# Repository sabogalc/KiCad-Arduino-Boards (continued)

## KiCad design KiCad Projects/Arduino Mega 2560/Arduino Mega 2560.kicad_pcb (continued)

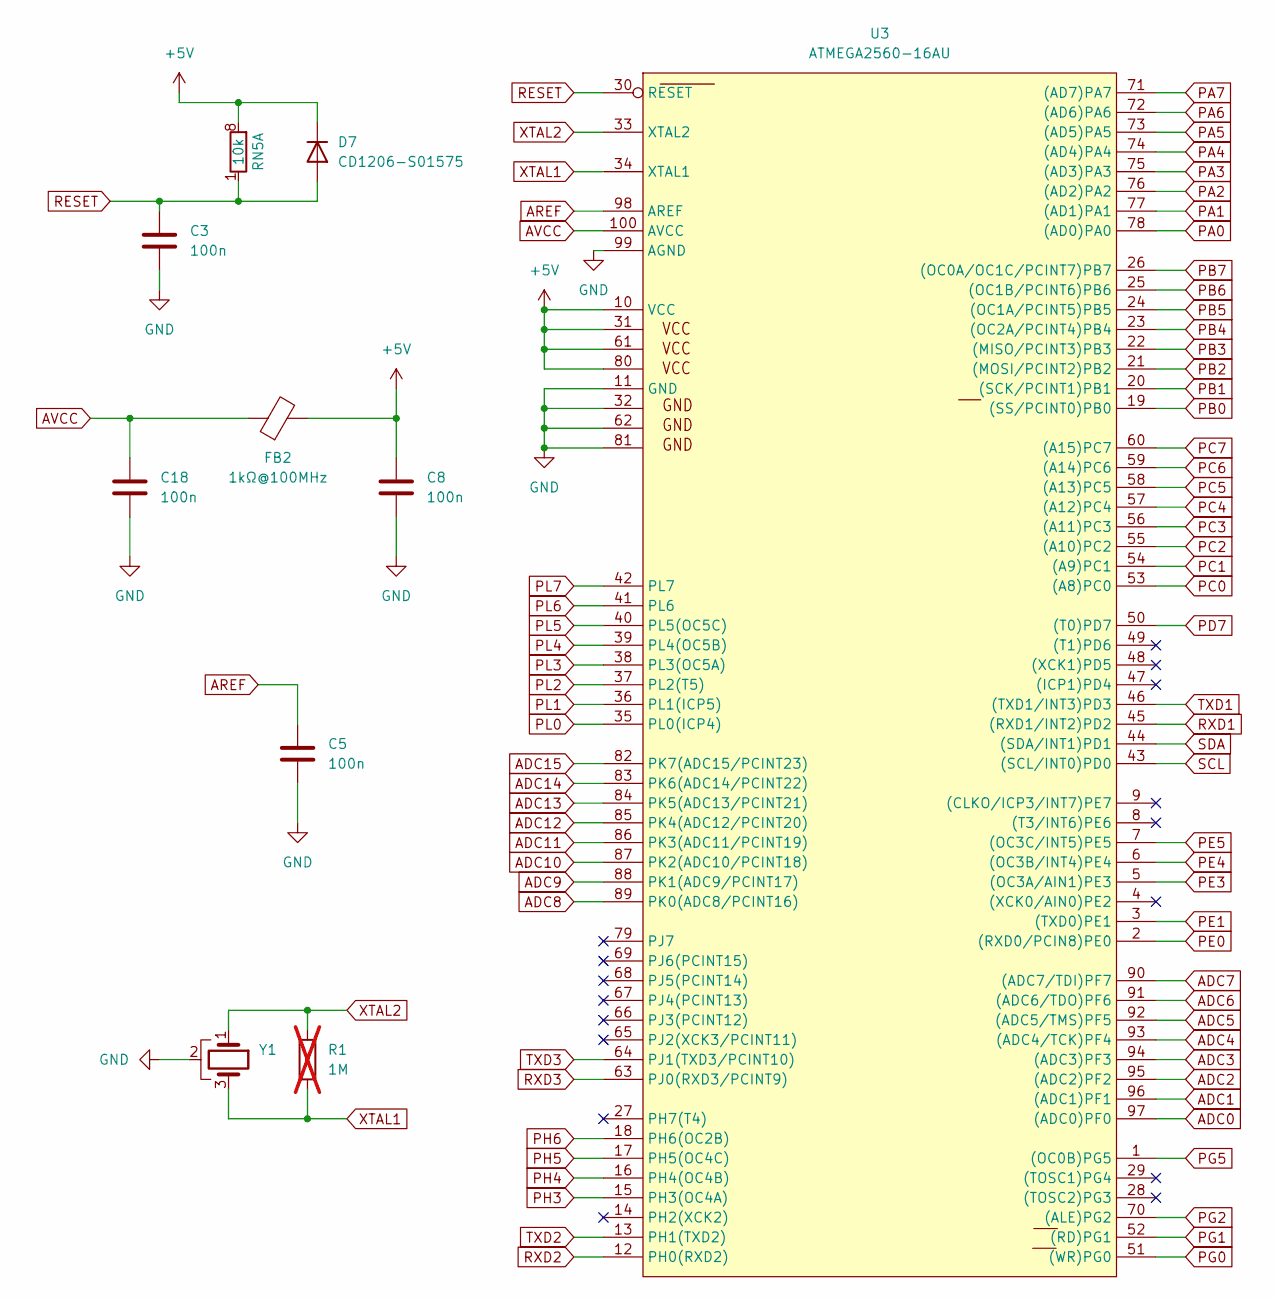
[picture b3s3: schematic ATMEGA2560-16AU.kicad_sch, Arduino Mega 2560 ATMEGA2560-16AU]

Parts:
C3, C5, C8, C18: 100n; C_0603_1608Metric
D7: CD1206-S01575; D_1206_3216Metric
FB2: 1kΩ@100MHz; L_0805_2012Metric
R1: 1M; R_0603_1608Metric; not fitted
RN5: 10k; R_Array_Convex_4x0612
U3: ATMEGA2560-16AU; TQFP-100_14x14mm_P0.5mm
Y1: CSTNE16M0V530000R0; Resonator_SMD_Murata_CSTxExxV-3Pin_3.0x1.1mm

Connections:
+5V: C8.1, D7.1 (K), FB2.2, RN5.8 (R1.2), U3.10 (VCC), U3.31 (VCC1), U3.61 (VCC2), U3.80 (VCC3); also elsewhere on the board
ADC0: U3.97 ((ADC0)PF0); also elsewhere on the board
ADC1: U3.96 ((ADC1)PF1); also elsewhere on the board
ADC2: U3.95 ((ADC2)PF2); also elsewhere on the board
ADC3: U3.94 ((ADC3)PF3); also elsewhere on the board
ADC4: U3.93 ((ADC4/TCK)PF4); also elsewhere on the board
ADC5: U3.92 ((ADC5/TMS)PF5); also elsewhere on the board
ADC6: U3.91 ((ADC6/TDO)PF6); also elsewhere on the board
ADC7: U3.90 ((ADC7/TDI)PF7); also elsewhere on the board
ADC8: U3.89 (PK0(ADC8/PCINT16)); also elsewhere on the board
ADC9: U3.88 (PK1(ADC9/PCINT17)); also elsewhere on the board
ADC10: U3.87 (PK2(ADC10/PCINT18)); also elsewhere on the board
ADC11: U3.86 (PK3(ADC11/PCINT19)); also elsewhere on the board
ADC12: U3.85 (PK4(ADC12/PCINT20)); also elsewhere on the board
ADC13: U3.84 (PK5(ADC13/PCINT21)); also elsewhere on the board
ADC14: U3.83 (PK6(ADC14/PCINT22)); also elsewhere on the board
ADC15: U3.82 (PK7(ADC15/PCINT23)); also elsewhere on the board
AREF: C5.1, U3.98 (AREF); also elsewhere on the board
AVCC: C18.1, FB2.1, U3.100 (AVCC)
GND: C3.2, C5.2, C8.2, C18.2, U3.11 (GND), U3.32 (GND1), U3.62 (GND2), U3.81 (GND3), U3.99 (AGND), Y1.2; also elsewhere on the board
PA0: U3.78 ((AD0)PA0); also elsewhere on the board
PA1: U3.77 ((AD1)PA1); also elsewhere on the board
PA2: U3.76 ((AD2)PA2); also elsewhere on the board
PA3: U3.75 ((AD3)PA3); also elsewhere on the board
PA4: U3.74 ((AD4)PA4); also elsewhere on the board
PA5: U3.73 ((AD5)PA5); also elsewhere on the board
PA6: U3.72 ((AD6)PA6); also elsewhere on the board
PA7: U3.71 ((AD7)PA7); also elsewhere on the board
PB0: U3.19 ((SS/PCINT0)PB0); also elsewhere on the board
PB1: U3.20 ((SCK/PCINT1)PB1); also elsewhere on the board
PB2: U3.21 ((MOSI/PCINT2)PB2); also elsewhere on the board
PB3: U3.22 ((MISO/PCINT3)PB3); also elsewhere on the board
PB4: U3.23 ((OC2A/PCINT4)PB4); also elsewhere on the board
PB5: U3.24 ((OC1A/PCINT5)PB5); also elsewhere on the board
PB6: U3.25 ((OC1B/PCINT6)PB6); also elsewhere on the board
PB7: U3.26 ((OC0A/OC1C/PCINT7)PB7); also elsewhere on the board
PC0: U3.53 ((A8)PC0); also elsewhere on the board
PC1: U3.54 ((A9)PC1); also elsewhere on the board
PC2: U3.55 ((A10)PC2); also elsewhere on the board
PC3: U3.56 ((A11)PC3); also elsewhere on the board
PC4: U3.57 ((A12)PC4); also elsewhere on the board
PC5: U3.58 ((A13)PC5); also elsewhere on the board
PC6: U3.59 ((A14)PC6); also elsewhere on the board
PC7: U3.60 ((A15)PC7); also elsewhere on the board
PD7: U3.50 ((T0)PD7); also elsewhere on the board
PE0: U3.2 ((RXD0/PCIN8)PE0); also elsewhere on the board
PE1: U3.3 ((TXD0)PE1); also elsewhere on the board
PE3: U3.5 ((OC3A/AIN1)PE3); also elsewhere on the board
PE4: U3.6 ((OC3B/INT4)PE4); also elsewhere on the board
PE5: U3.7 ((OC3C/INT5)PE5); also elsewhere on the board
PG0: U3.51 ((WR)PG0); also elsewhere on the board
PG1: U3.52 ((RD)PG1); also elsewhere on the board
PG2: U3.70 ((ALE)PG2); also elsewhere on the board
PG5: U3.1 ((OC0B)PG5); also elsewhere on the board
PH3: U3.15 (PH3(OC4A)); also elsewhere on the board
PH4: U3.16 (PH4(OC4B)); also elsewhere on the board
PH5: U3.17 (PH5(OC4C)); also elsewhere on the board
PH6: U3.18 (PH6(OC2B)); also elsewhere on the board
PL0: U3.35 (PL0(ICP4)); also elsewhere on the board
PL1: U3.36 (PL1(ICP5)); also elsewhere on the board
PL2: U3.37 (PL2(T5)); also elsewhere on the board
PL3: U3.38 (PL3(OC5A)); also elsewhere on the board
PL4: U3.39 (PL4(OC5B)); also elsewhere on the board
PL5: U3.40 (PL5(OC5C)); also elsewhere on the board
PL6: U3.41 (PL6); also elsewhere on the board
PL7: U3.42 (PL7); also elsewhere on the board
RESET: C3.1, D7.2 (A), RN5.1 (R1.1), U3.30 (RESET); also elsewhere on the board
RXD1: U3.45 ((RXD1/INT2)PD2); also elsewhere on the board
RXD2: U3.12 (PH0(RXD2)); also elsewhere on the board
RXD3: U3.63 (PJ0(RXD3/PCINT9)); also elsewhere on the board
SCL: U3.43 ((SCL/INT0)PD0); also elsewhere on the board
SDA: U3.44 ((SDA/INT1)PD1); also elsewhere on the board
TXD1: U3.46 ((TXD1/INT3)PD3); also elsewhere on the board
TXD2: U3.13 (PH1(TXD2)); also elsewhere on the board
TXD3: U3.64 (PJ1(TXD3/PCINT10)); also elsewhere on the board
XTAL1: R1.1, U3.34 (XTAL1), Y1.3
XTAL2: R1.2, U3.33 (XTAL2), Y1.1

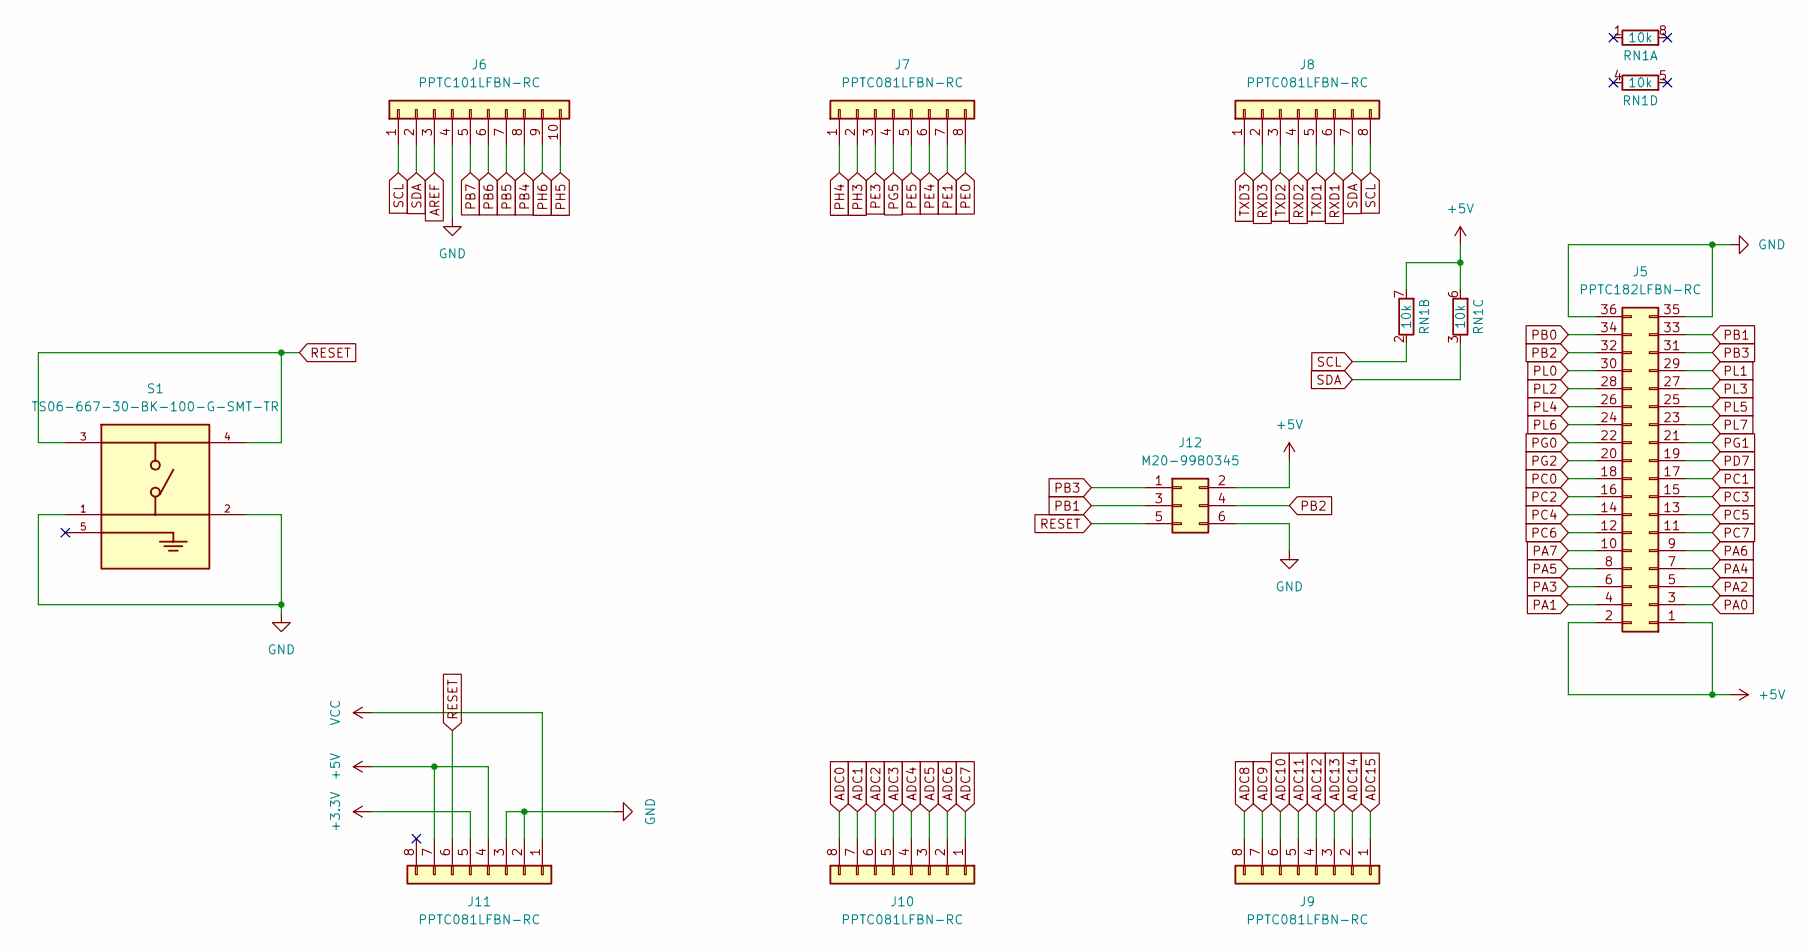
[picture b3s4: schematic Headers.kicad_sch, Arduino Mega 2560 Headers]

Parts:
J5: PPTC182LFBN-RC
J6: PPTC101LFBN-RC; PinSocket_1x10_P2.54mm_Vertical
J7, J8, J9, J10, J11: PPTC081LFBN-RC; PinSocket_1x08_P2.54mm_Vertical
J12: M20-9980345; PinHeader_2x03_P2.54mm_Vertical
RN1: 10k; R_Array_Convex_4x0612
S1: TS06-667-30-BK-100-G-SMT-TR; SW_TS06-667-30-BK-100-G-SMT-TR; PARTREV 1.0

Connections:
+3.3V: J11.5; also elsewhere on the board
+5V: J5.1, J5.2, J11.4, J11.7, J12.2, RN1.6 (R3.2), RN1.7 (R2.2); also elsewhere on the board
ADC0: J10.8; also elsewhere on the board
ADC1: J10.7; also elsewhere on the board
ADC2: J10.6; also elsewhere on the board
ADC3: J10.5; also elsewhere on the board
ADC4: J10.4; also elsewhere on the board
ADC5: J10.3; also elsewhere on the board
ADC6: J10.2; also elsewhere on the board
ADC7: J10.1; also elsewhere on the board
ADC8: J9.8; also elsewhere on the board
ADC9: J9.7; also elsewhere on the board
ADC10: J9.6; also elsewhere on the board
ADC11: J9.5; also elsewhere on the board
ADC12: J9.4; also elsewhere on the board
ADC13: J9.3; also elsewhere on the board
ADC14: J9.2; also elsewhere on the board
ADC15: J9.1; also elsewhere on the board
AREF: J6.3; also elsewhere on the board
GND: J5.35, J5.36, J6.4, J11.2, J11.3, J12.6, S1.1, S1.2; also elsewhere on the board
PA0: J5.3; also elsewhere on the board
PA1: J5.4; also elsewhere on the board
PA2: J5.5; also elsewhere on the board
PA3: J5.6; also elsewhere on the board
PA4: J5.7; also elsewhere on the board
PA5: J5.8; also elsewhere on the board
PA6: J5.9; also elsewhere on the board
PA7: J5.10; also elsewhere on the board
PB0: J5.34; also elsewhere on the board
PB1: J5.33, J12.3; also elsewhere on the board
PB2: J5.32, J12.4; also elsewhere on the board
PB3: J5.31, J12.1; also elsewhere on the board
PB4: J6.8; also elsewhere on the board
PB5: J6.7; also elsewhere on the board
PB6: J6.6; also elsewhere on the board
PB7: J6.5; also elsewhere on the board
PC0: J5.18; also elsewhere on the board
PC1: J5.17; also elsewhere on the board
PC2: J5.16; also elsewhere on the board
PC3: J5.15; also elsewhere on the board
PC4: J5.14; also elsewhere on the board
PC5: J5.13; also elsewhere on the board
PC6: J5.12; also elsewhere on the board
PC7: J5.11; also elsewhere on the board
PD7: J5.19; also elsewhere on the board
PE0: J7.8; also elsewhere on the board
PE1: J7.7; also elsewhere on the board
PE3: J7.3; also elsewhere on the board
PE4: J7.6; also elsewhere on the board
PE5: J7.5; also elsewhere on the board
PG0: J5.22; also elsewhere on the board
PG1: J5.21; also elsewhere on the board
PG2: J5.20; also elsewhere on the board
PG5: J7.4; also elsewhere on the board
PH3: J7.2; also elsewhere on the board
PH4: J7.1; also elsewhere on the board
PH5: J6.10; also elsewhere on the board
PH6: J6.9; also elsewhere on the board
PL0: J5.30; also elsewhere on the board
PL1: J5.29; also elsewhere on the board
PL2: J5.28; also elsewhere on the board
PL3: J5.27; also elsewhere on the board
PL4: J5.26; also elsewhere on the board
PL5: J5.25; also elsewhere on the board
PL6: J5.24; also elsewhere on the board
PL7: J5.23; also elsewhere on the board
RESET: J11.6, J12.5, S1.3, S1.4; also elsewhere on the board
RXD1: J8.6; also elsewhere on the board
RXD2: J8.4; also elsewhere on the board
RXD3: J8.2; also elsewhere on the board
SCL: J6.1, J8.8, RN1.2 (R2.1); also elsewhere on the board
SDA: J6.2, J8.7, RN1.3 (R3.1); also elsewhere on the board
TXD1: J8.5; also elsewhere on the board
TXD2: J8.3; also elsewhere on the board
TXD3: J8.1; also elsewhere on the board
VCC: J11.1; also elsewhere on the board

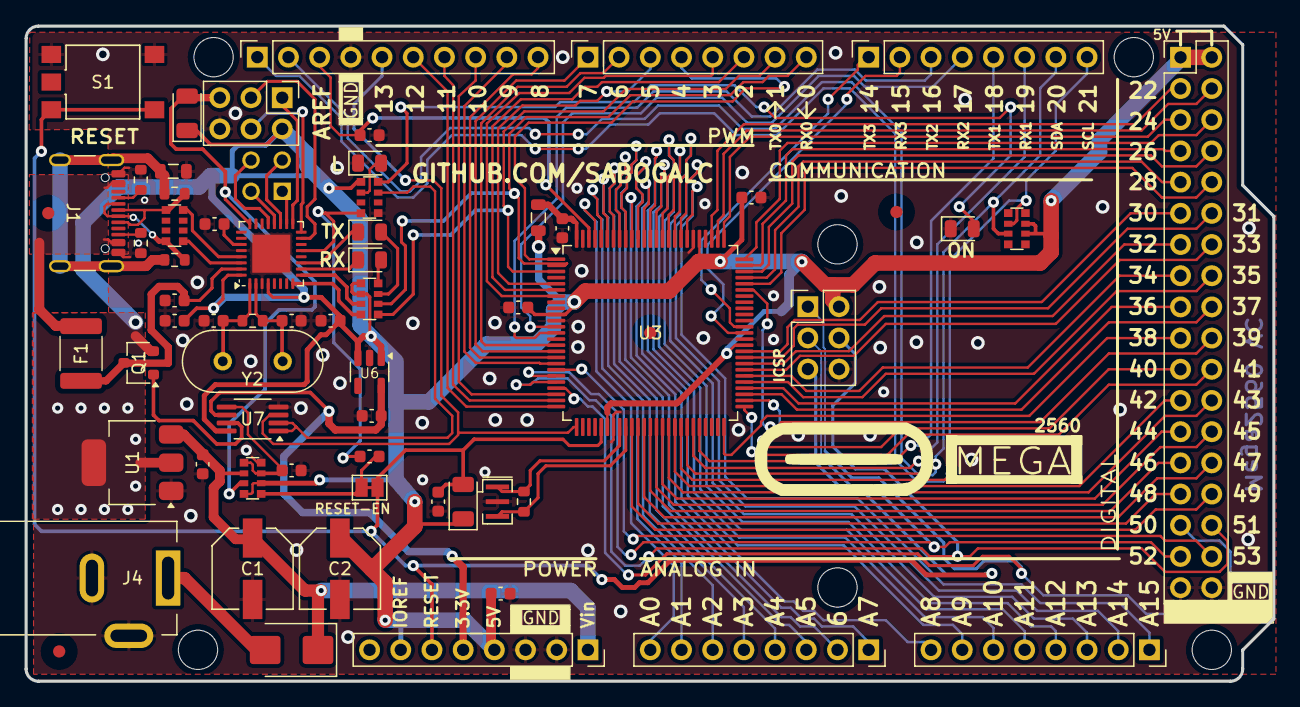
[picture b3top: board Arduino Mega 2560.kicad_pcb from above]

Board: 2 copper layers, 101.6 x 53.3 mm, 66 parts (1 on the bottom side), 112 nets.

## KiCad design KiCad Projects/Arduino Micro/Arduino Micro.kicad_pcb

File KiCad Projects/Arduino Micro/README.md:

# Micro
Much like the Nano, I made this board in one or two sittings.

This board is not much bigger than the Nano, but it brings benefits such as the full-sized reset switch and four more IO pins.

## KiCad 3D View
Below are the screenshots of this board from KiCad's 3D board viewer.

## Real-World Application
Additionally, I have successfully built this board in real life and confirmed that it works.

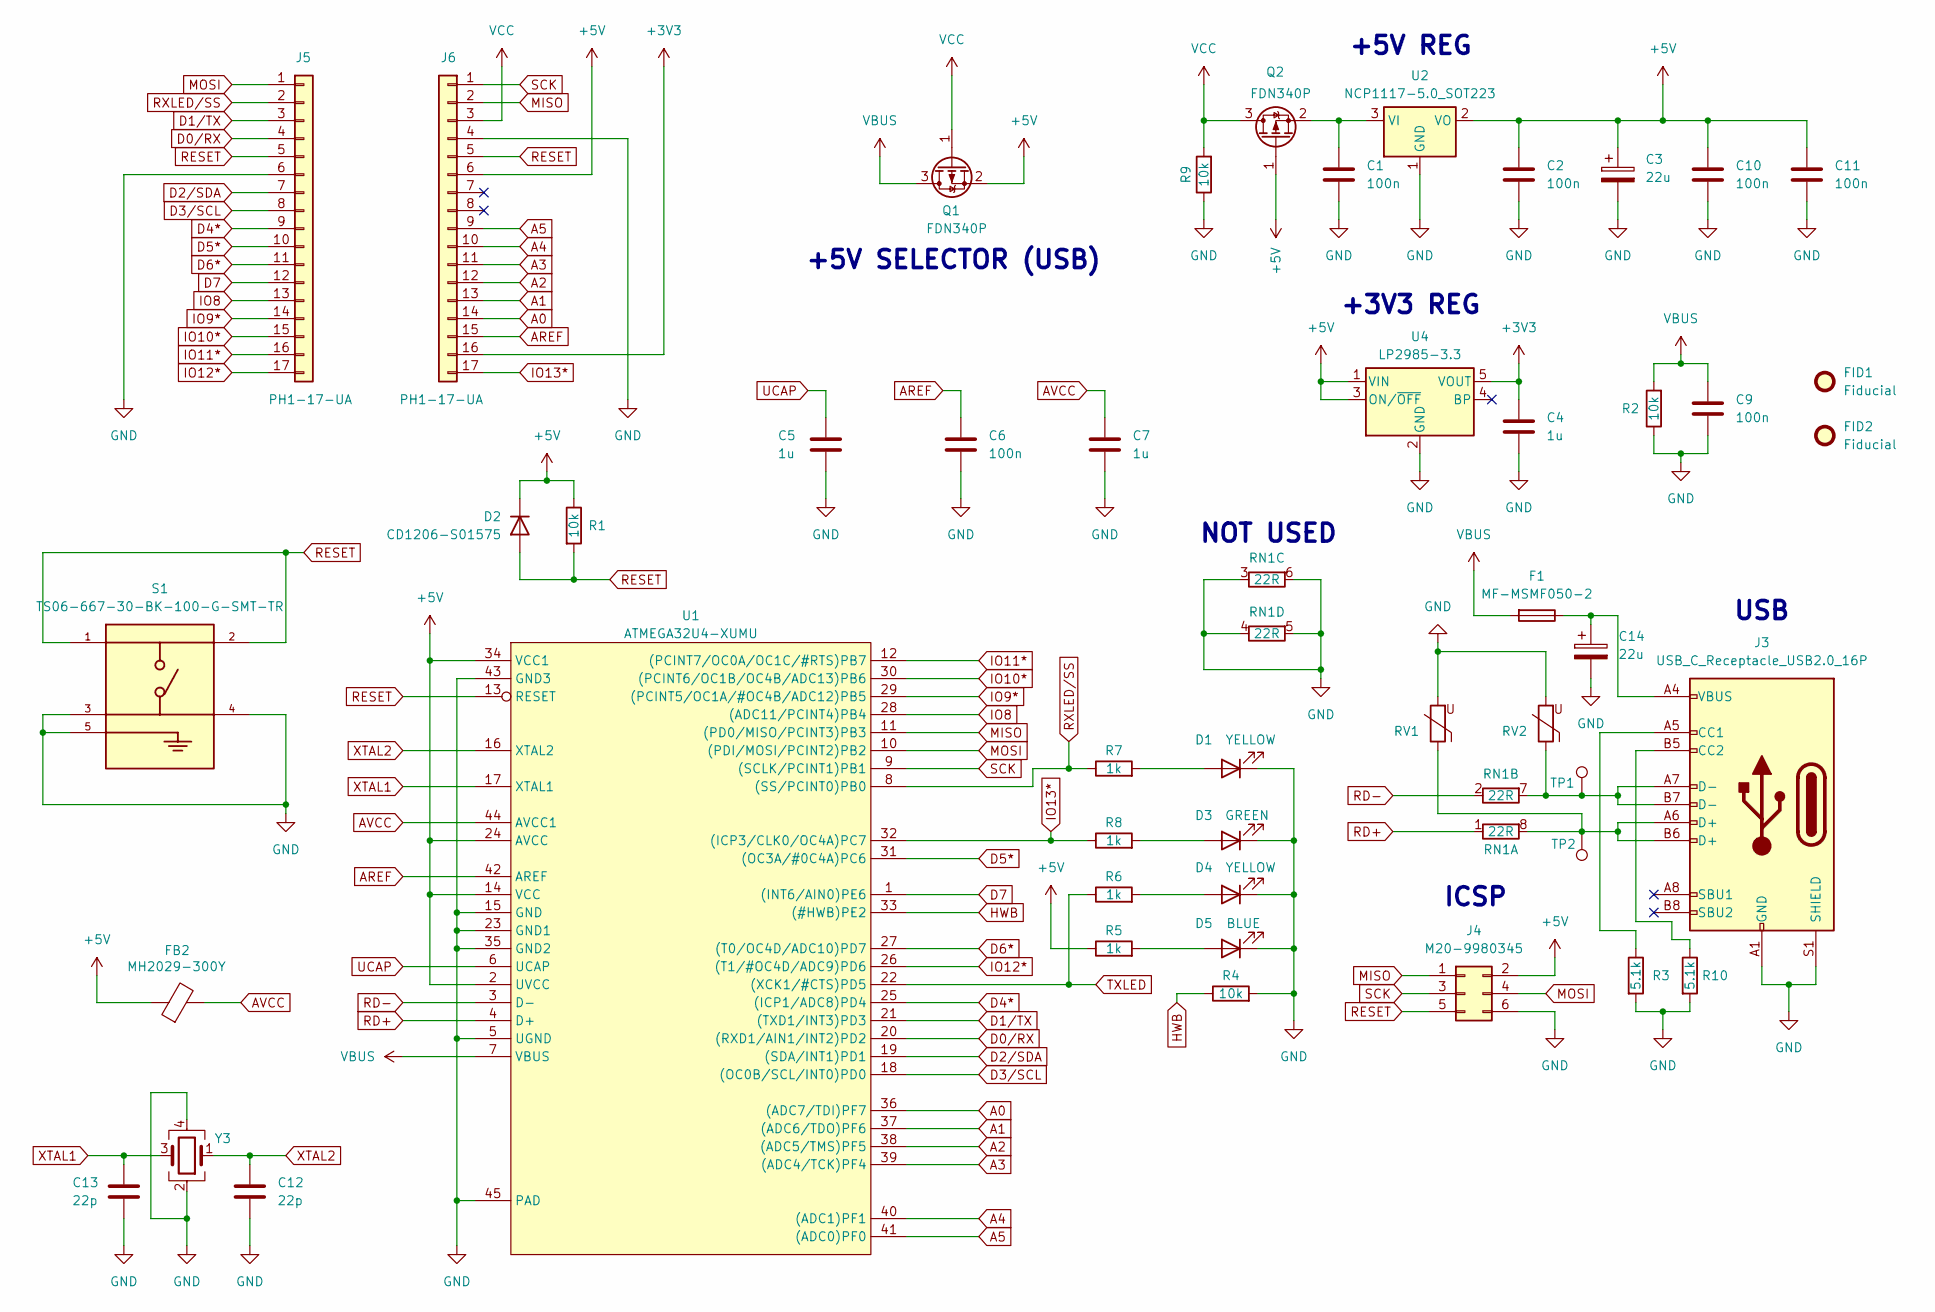
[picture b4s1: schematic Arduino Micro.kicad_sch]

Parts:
C1, C2, C6, C9, C10, C11: 100n; C_0402_1005Metric
C3, C14: 22u; C_1210_3225Metric_Pad1.33x2.70mm_HandSolder
C4, C5, C7: 1u; C_0402_1005Metric
C12, C13: 22p; C_0402_1005Metric
D1, D4: YELLOW; LED_0805_2012Metric
D2: CD1206-S01575; D_1206_3216Metric
D3: GREEN; LED_0805_2012Metric
D5: BLUE; LED_0805_2012Metric
F1: MF-MSMF050-2; Fuse_1812_4532Metric_Pad1.30x3.40mm_HandSolder
FB2: MH2029-300Y; L_0805_2012Metric
FID1, FID2: Fiducial; Fiducial_1mm_Mask2mm
J3: USB_C_Receptacle_USB2.0_16P; USB_C_Receptacle_GCT_USB4110
J4: M20-9980345; PinHeader_2x03_P2.54mm_Vertical
J5, J6: PH1-17-UA; PinHeader_1x17_P2.54mm_Vertical
Q1, Q2: FDN340P; SC-59
R1, R2, R4, R9: 10k; R_0402_1005Metric
R3, R10: 5.1k; R_0402_1005Metric
R5, R6, R7, R8: 1k; R_0402_1005Metric
RN1: 22R; R_Array_Convex_4x0612
RV1, RV2: CG0603MLC-05E; R_0603_1608Metric
S1: TS06-667-30-BK-100-G-SMT-TR; SW_TS06-667-30-BK-100-G-SMT-TR; PARTREV 1.0
TP1, TP2: TestPoint; TestPoint_Pad_D1.0mm
U1: ATMEGA32U4-XUMU; TQFN-44-1EP_7x7mm_P0.5mm_EP4.7x4.7mm
U2: NCP1117-5.0_SOT223; SOT-223-3_TabPin2
U4: LP2985-3.3; SOT-23-5
Y3: ECS-160-18-33-JGN-TR; Crystal_SMD_SeikoEpson_FA238-4Pin_3.2x2.5mm

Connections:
+3V3: C4.1, J6.16, U4.5 (VOUT)
+5V: C2.1, C3.1, C10.1, C11.1, D2.1 (K), FB2.1, J4.2, J6.6, Q1.2 (S), Q2.1 (G), R1.1, R5.1, U1.2 (UVCC), U1.14 (VCC), U1.24 (AVCC), U1.34 (VCC1), U2.2 (VO), U4.1 (VIN), U4.3 (ON/~OFF)
A0: J6.14, U1.36 ((ADC7/TDI)PF7)
A1: J6.13, U1.37 ((ADC6/TDO)PF6)
A2: J6.12, U1.38 ((ADC5/TMS)PF5)
A3: J6.11, U1.39 ((ADC4/TCK)PF4)
A4: J6.10, U1.40 ((ADC1)PF1)
A5: J6.9, U1.41 ((ADC0)PF0)
AREF: C6.1, J6.15, U1.42 (AREF)
AVCC: C7.1, FB2.2, U1.44 (AVCC1)
D0/RX: J5.4, U1.20 ((RXD1/AIN1/INT2)PD2)
D1/TX: J5.3, U1.21 ((TXD1/INT3)PD3)
D2/SDA: J5.7, U1.19 ((SDA/INT1)PD1)
D3/SCL: J5.8, U1.18 ((OC0B/SCL/INT0)PD0)
D4*: J5.9, U1.25 ((ICP1/ADC8)PD4)
D5*: J5.10, U1.31 ((OC3A/#0C4A)PC6)
D6*: J5.11, U1.27 ((T0/OC4D/ADC10)PD7)
D7: J5.12, U1.1 ((INT6/AIN0)PE6)
GND: C1.2, C2.2, C3.2, C4.2, C5.2, C6.2, C7.2, C9.2, C10.2, C11.2, C12.1, C13.1, C14.2, D1.1 (K), D3.1 (K), D4.1 (K), D5.1 (K), J3.A1 (GND), J3.A12 (GND), J3.B1 (GND), J3.B12 (GND), J3.S1 (SHIELD), J4.6, J5.6, J6.4, R2.1, R3.2, R4.2, R9.1, R10.2, RN1.3 (R3.1), RN1.4 (R4.1), RN1.5 (R4.2), RN1.6 (R3.2), RV1.2, RV2.2, S1.3, S1.4, S1.5, U1.5 (UGND), U1.15 (GND), U1.23 (GND1), U1.35 (GND2), U1.43 (GND3), U1.45 (PAD), U2.1 (GND), U4.2 (GND), Y3.2, Y3.4
HWB: R4.1, U1.33 ((#HWB)PE2)
IO8: J5.13, U1.28 ((ADC11/PCINT4)PB4)
IO9*: J5.14, U1.29 ((PCINT5/OC1A/#OC4B/ADC12)PB5)
IO10*: J5.15, U1.30 ((PCINT6/OC1B/OC4B/ADC13)PB6)
IO11*: J5.16, U1.12 ((PCINT7/OC0A/OC1C/#RTS)PB7)
IO12*: J5.17, U1.26 ((T1/#OC4D/ADC9)PD6)
IO13*: J6.17, R8.1, U1.32 ((ICP3/CLK0/OC4A)PC7)
MISO: J4.1, J6.2, U1.11 ((PD0/MISO/PCINT3)PB3)
MOSI: J4.4, J5.1, U1.10 ((PDI/MOSI/PCINT2)PB2)
unnamed: C14.1, F1.1, J3.A4 (VBUS), J3.A9 (VBUS), J3.B4 (VBUS), J3.B9 (VBUS)
unnamed: D1.2 (A), R7.2
unnamed: D3.2 (A), R8.2
unnamed: D4.2 (A), R6.2
unnamed: D5.2 (A), R5.2
unnamed: J3.A5 (CC1), R3.1
unnamed: J3.B5 (CC2), R10.1
unnamed: C1.1, Q2.2 (S), U2.3 (VI)
unnamed: J3.A6 (D+), J3.B6 (D+), RN1.8 (R1.2), RV1.1, TP2.1
unnamed: J3.A7 (D-), J3.B7 (D-), RN1.7 (R2.2), RV2.1, TP1.1
RD+: RN1.1 (R1.1), U1.4 (D+)
RD-: RN1.2 (R2.1), U1.3 (D-)
RESET: D2.2 (A), J4.5, J5.5, J6.5, R1.2, S1.1, S1.2, U1.13 (RESET)
RXLED/SS: J5.2, R7.1, U1.8 ((SS/PCINT0)PB0)
SCK: J4.3, J6.1, U1.9 ((SCLK/PCINT1)PB1)
TXLED: R6.1, U1.22 ((XCK1/#CTS)PD5)
UCAP: C5.1, U1.6 (UCAP)
VBUS: C9.1, F1.2, Q1.3 (D), R2.2, U1.7 (VBUS)
VCC: J6.3, Q1.1 (G), Q2.3 (D), R9.2
XTAL1: C13.2, U1.17 (XTAL1), Y3.3
XTAL2: C12.2, U1.16 (XTAL2), Y3.1

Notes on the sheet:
ICSP
+3V3 REG
+5V REG
NOT USED
USB
+5V SELECTOR (USB)

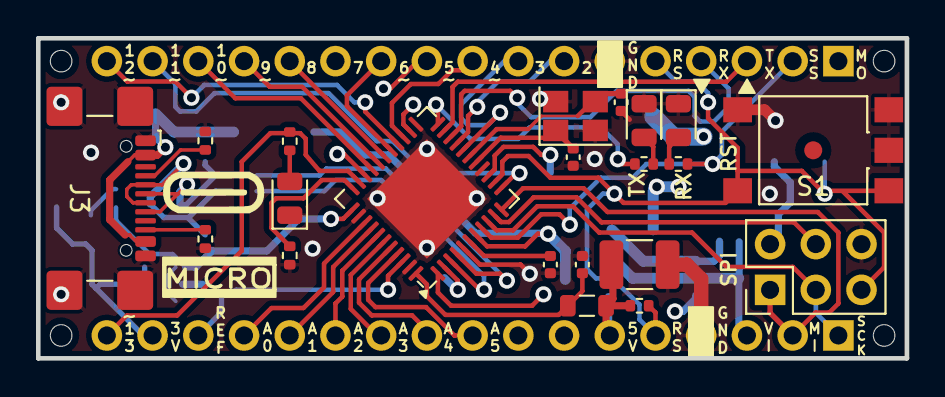
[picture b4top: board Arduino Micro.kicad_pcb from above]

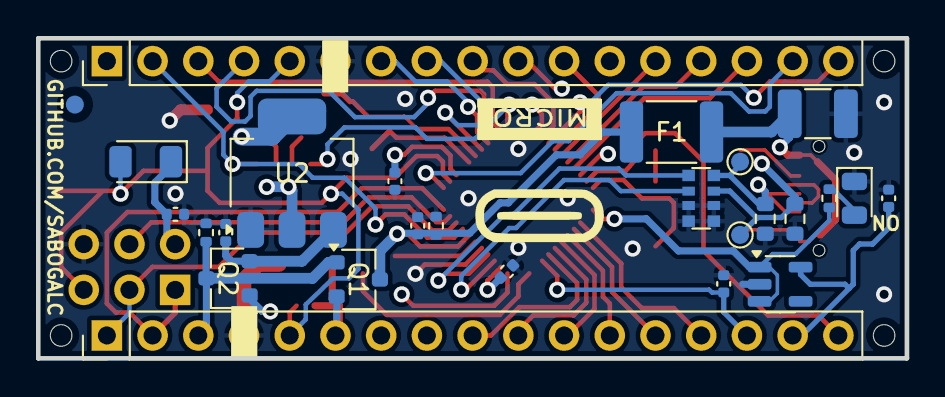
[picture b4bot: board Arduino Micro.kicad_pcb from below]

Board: 4 copper layers, 48.3 x 17.8 mm, 48 parts (26 on the bottom side), 49 nets.

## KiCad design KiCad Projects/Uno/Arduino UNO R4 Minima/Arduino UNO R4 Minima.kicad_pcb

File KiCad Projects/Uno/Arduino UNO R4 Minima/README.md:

# UNO R4 Minima

## Overview
This board was very straightforward to make, and it is almost 1:1 with the factory one. Even though the UNO R4 already comes with USB-C from Arduino, the OEM footprint is one that exposes the middle plastic receptacle a bit, so I replaced it with one that has the entire port enclosed.

## Design Considerations
While working on this board, I encountered a few challenges:

- **Silkscreen Squares:** The silkscreen square etches on the left side were a bit cumbersome to design.
- **Microcontroller Routing:** Routing beneath the R7FA4M1AB3CFM#AA0 microcontroller was also relatively intricate, as seen below.

## KiCad 3D View
Below are the screenshots of this board from KiCad's 3D board viewer.

## Real-World Application
I have successfully built this board and confirmed that it works.

### Important Note on Soldering
During assembly, I had to solder the buck regulator on 3 separate times since I kept blowing it up. As seen in the [ISL854102 datasheet](https://www.renesas.com/en/document/dst/isl854102-datasheet), its pin configuration is as follows:

- Pin 4: V<sub>in</sub>
- Pin 5: V<sub>out</sub>
- Pin 6: GND

Naturally, shorting any one of these pins to the other can cause a detrimental short, and the 0.5mm pitch makes it easy to do so. Please be careful when soldering the buck regulator!

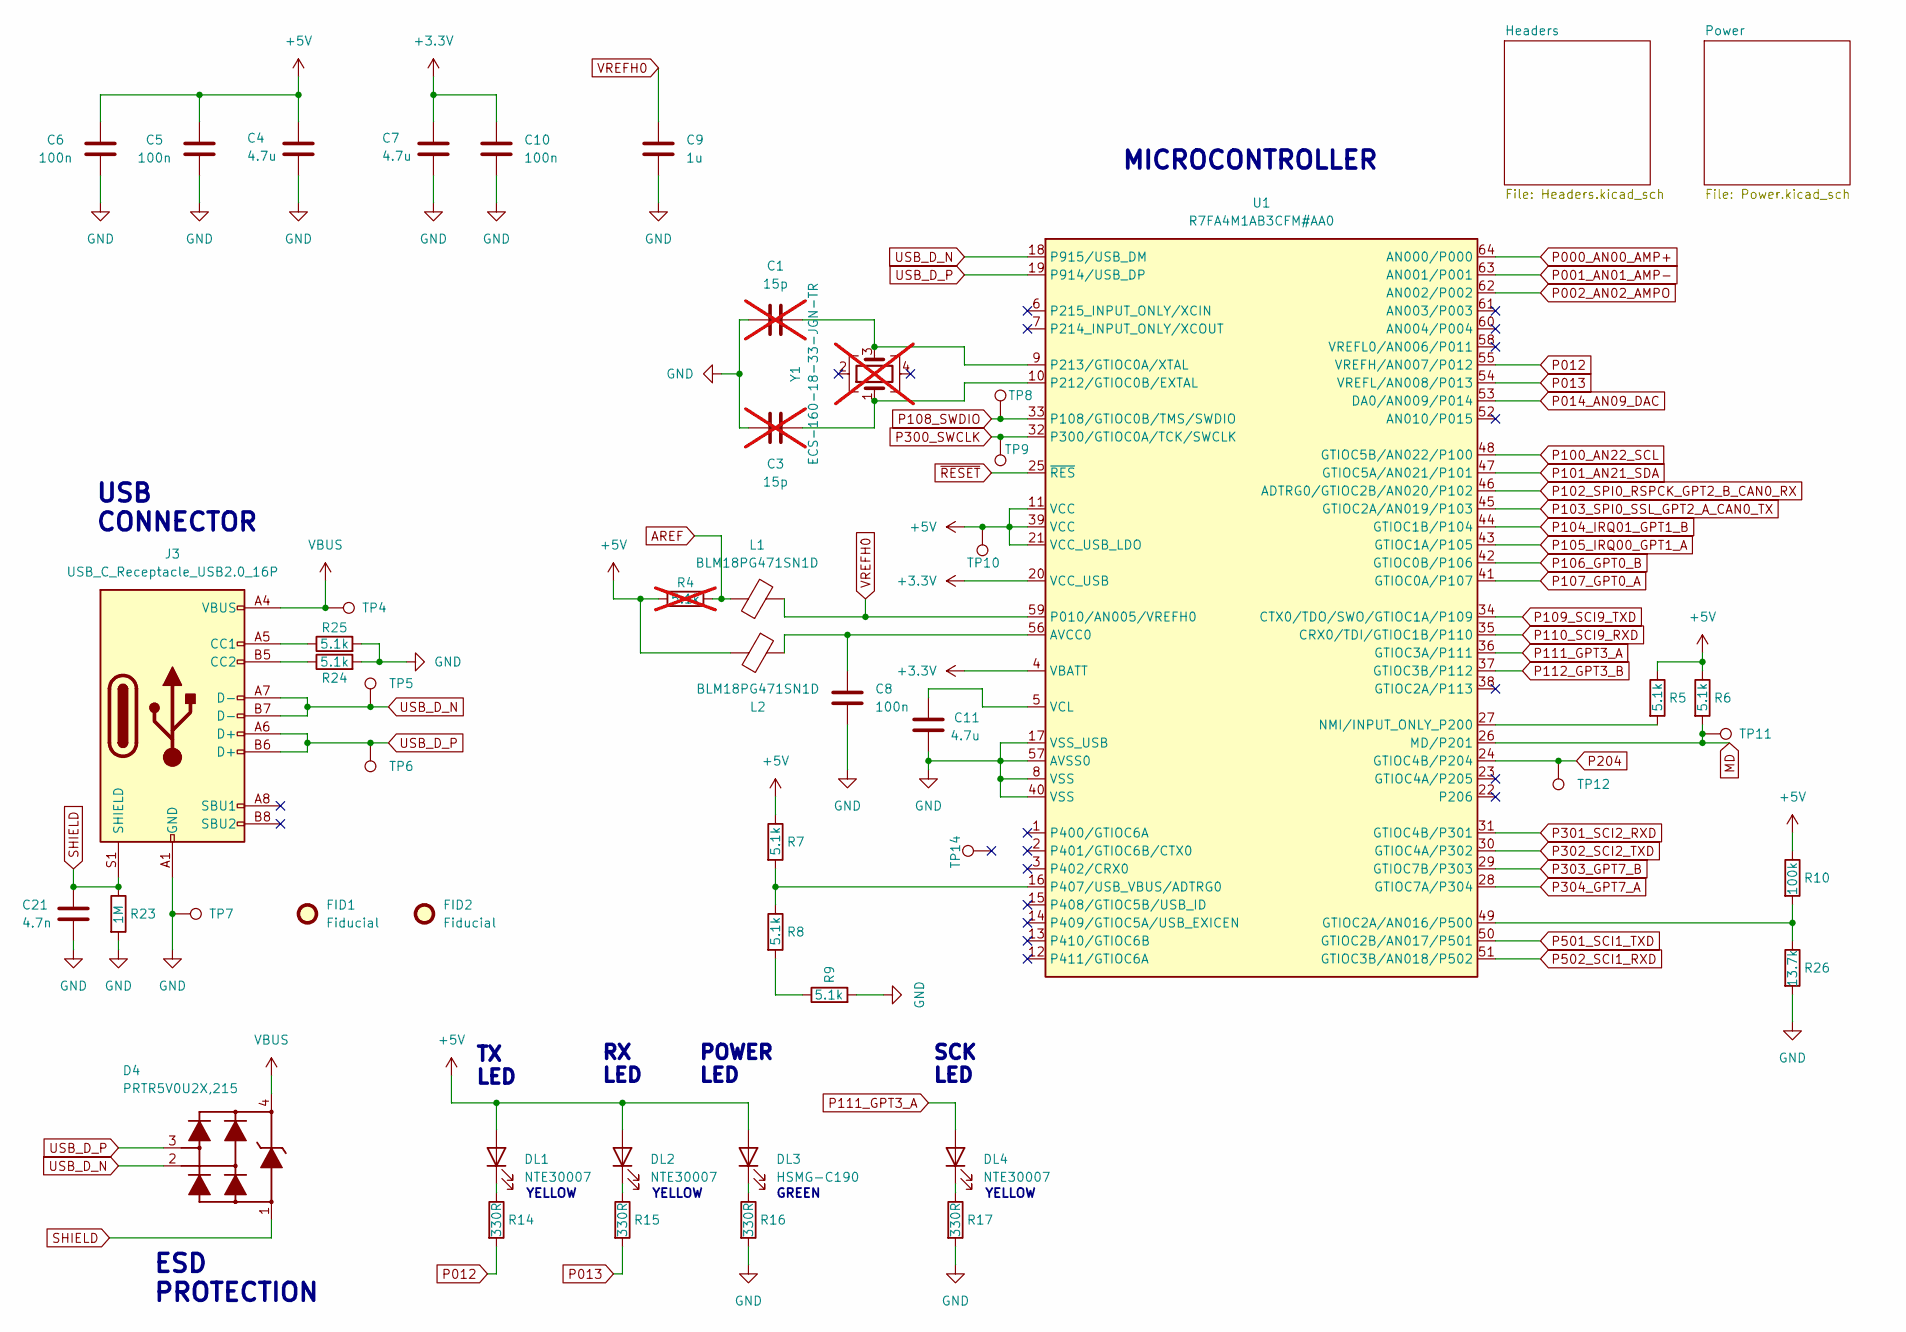
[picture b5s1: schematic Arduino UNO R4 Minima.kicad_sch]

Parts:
C1, C3: 15p; C_0402_1005Metric; not fitted
C4, C7, C11: 4.7u; C_0603_1608Metric
C5, C6, C8, C10: 100n; C_0402_1005Metric
C9: 1u; C_0402_1005Metric
C21: 4.7n; C_0805_2012Metric
D4: PRTR5V0U2X,215; SOT-143
DL1, DL2, DL4: NTE30007; LED_0603_1608Metric
DL3: HSMG-C190; LED_0603_1608Metric
FID1, FID2: Fiducial; Fiducial_1mm_Mask2mm
J3: USB_C_Receptacle_USB2.0_16P; USB_C_Receptacle_GCT_USB4105-xx-A_16P_TopMnt_Horizontal
L1, L2: BLM18PG471SN1D; L_0603_1608Metric
R4: 5.1k; R_0402_1005Metric; not fitted
R5, R6, R7, R8, R9, R24, R25: 5.1k; R_0402_1005Metric
R10: 100k; R_0402_1005Metric
R14, R15, R16, R17: 330R; R_0402_1005Metric
R23: 1M; R_0402_1005Metric
R26: 13.7k; R_0402_1005Metric
TP4, TP5, TP6, TP7, TP8, TP9, TP10, TP11, TP14: TestPoint; TestPoint_Pad_D1.0mm
TP12: TestPoint; TestPoint_P204
U1: R7FA4M1AB3CFM#AA0; LQFP-64_10x10mm_P0.5mm
Y1: ECS-160-18-33-JGN-TR; Crystal_SMD_SeikoEpson_FA238-4Pin_3.2x2.5mm; not fitted

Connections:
+3.3V: C7.1, C10.1, U1.4 (VBATT), U1.20 (VCC_USB); also elsewhere on the board
+5V: C4.1, C5.1, C6.1, DL1.2 (A), DL2.2 (A), DL3.2 (A), L2.2, R4.1, R5.1, R6.1, R7.1, R10.1, TP10.1, U1.11 (VCC), U1.21 (VCC_USB_LDO), U1.39 (VCC); also elsewhere on the board
AREF: L1.1, R4.2; also elsewhere on the board
GND: C1.1, C3.1, C4.2, C5.2, C6.2, C7.2, C8.2, C9.2, C10.2, C11.1, C21.2, J3.A1 (GND), J3.A12 (GND), J3.B1 (GND), J3.B12 (GND), R9.2, R16.2, R17.2, R23.2, R24.2, R25.2, R26.2, TP7.1, U1.8 (VSS), U1.17 (VSS_USB), U1.40 (VSS), U1.57 (AVSS0); also elsewhere on the board
MD: R6.2, TP11.1, U1.26 (MD/P201); also elsewhere on the board
unnamed: DL1.1 (K), R14.1
unnamed: DL2.1 (K), R15.1
unnamed: DL3.1 (K), R16.1
unnamed: DL4.1 (K), R17.1
unnamed: J3.A5 (CC1), R25.1
unnamed: J3.B5 (CC2), R24.1
unnamed: R8.2, R9.1
unnamed: C8.1, L2.1, U1.56 (AVCC0)
unnamed: R10.2, R26.1, U1.49 (GTIOC2A/AN016/P500)
unnamed: R5.2, U1.27 (NMI/INPUT_ONLY_P200)
unnamed: C3.2, U1.10 (P212/GTIOC0B/EXTAL), Y1.1
unnamed: C1.2, U1.9 (P213/GTIOC0A/XTAL), Y1.3
unnamed: R7.2, R8.1, U1.16 (P407/USB_VBUS/ADTRG0)
unnamed: C11.2, U1.5 (VCL)
P000_AN00_AMP+: U1.64 (AN000/P000); also elsewhere on the board
P001_AN01_AMP-: U1.63 (AN001/P001); also elsewhere on the board
P002_AN02_AMPO: U1.62 (AN002/P002); also elsewhere on the board
P012: R14.2, U1.55 (VREFH/AN007/P012)
P013: R15.2, U1.54 (VREFL/AN008/P013)
P014_AN09_DAC: U1.53 (DA0/AN009/P014); also elsewhere on the board
P100_AN22_SCL: U1.48 (GTIOC5B/AN022/P100); also elsewhere on the board
P101_AN21_SDA: U1.47 (GTIOC5A/AN021/P101); also elsewhere on the board
P102_SPI0_RSPCK_GPT2_B_CAN0_RX: U1.46 (ADTRG0/GTIOC2B/AN020/P102); also elsewhere on the board
P103_SPI0_SSL_GPT2_A_CAN0_TX: U1.45 (GTIOC2A/AN019/P103); also elsewhere on the board
P104_IRQ01_GPT1_B: U1.44 (GTIOC1B/P104); also elsewhere on the board
P105_IRQ00_GPT1_A: U1.43 (GTIOC1A/P105); also elsewhere on the board
P106_GPT0_B: U1.42 (GTIOC0B/P106); also elsewhere on the board
P107_GPT0_A: U1.41 (GTIOC0A/P107); also elsewhere on the board
P108_SWDIO: TP8.1, U1.33 (P108/GTIOC0B/TMS/SWDIO); also elsewhere on the board
P109_SCI9_TXD: U1.34 (CTX0/TDO/SWO/GTIOC1A/P109); also elsewhere on the board
P110_SCI9_RXD: U1.35 (CRX0/TDI/GTIOC1B/P110); also elsewhere on the board
P111_GPT3_A: DL4.2 (A), U1.36 (GTIOC3A/P111); also elsewhere on the board
P112_GPT3_B: U1.37 (GTIOC3B/P112); also elsewhere on the board
P204: TP12.1, U1.24 (GTIOC4B/P204)
P300_SWCLK: TP9.1, U1.32 (P300/GTIOC0A/TCK/SWCLK); also elsewhere on the board
P301_SCI2_RXD: U1.31 (GTIOC4B/P301); also elsewhere on the board
P302_SCI2_TXD: U1.30 (GTIOC4A/P302); also elsewhere on the board
P303_GPT7_B: U1.29 (GTIOC7B/P303); also elsewhere on the board
P304_GPT7_A: U1.28 (GTIOC7A/P304); also elsewhere on the board
P501_SCI1_TXD: U1.50 (GTIOC2B/AN017/P501); also elsewhere on the board
P502_SCI1_RXD: U1.51 (GTIOC3B/AN018/P502); also elsewhere on the board
SHIELD: C21.1, D4.1, J3.S1 (SHIELD), R23.1
USB_D_N: D4.2, J3.A7 (D-), J3.B7 (D-), TP5.1, U1.18 (P915/USB_DM)
USB_D_P: D4.3, J3.A6 (D+), J3.B6 (D+), TP6.1, U1.19 (P914/USB_DP)
VBUS: D4.4, J3.A4 (VBUS), J3.A9 (VBUS), J3.B4 (VBUS), J3.B9 (VBUS), TP4.1; also elsewhere on the board
VREFH0: C9.1, L1.2, U1.59 (P010/AN005/VREFH0)
~RESET: U1.25 (~RES); also elsewhere on the board

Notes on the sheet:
RX LED
SCK LED
ESD PROTECTION
TX LED
YELLOW
MICROCONTROLLER
USB CONNECTOR
GREEN
POWER LED

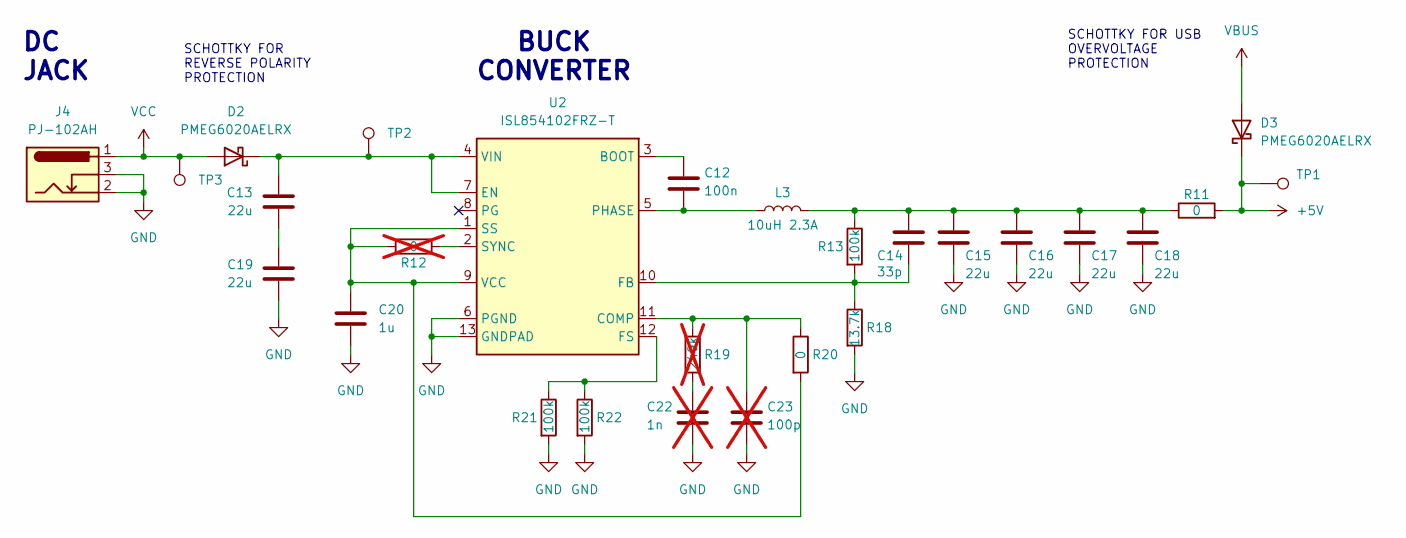
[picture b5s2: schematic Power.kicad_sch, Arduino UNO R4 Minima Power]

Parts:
C12: 100n; C_0402_1005Metric
C13, C15, C16, C17, C18, C19: 22u; C_0805_2012Metric
C14: 33p; C_0402_1005Metric
C20: 1u; C_0402_1005Metric
C22: 1n; C_0402_1005Metric; not fitted
C23: 100p; C_0402_1005Metric; not fitted
D2, D3: PMEG6020AELRX; D_SOD-123
J4: PJ-102AH; BarrelJack_Kycon_KLDX-0202-xC_Horizontal
L3: 10uH 2.3A; PMF42-103MN
R11, R20: 0; R_0402_1005Metric
R12: 0; R_0402_1005Metric; not fitted
R13, R21, R22: 100k; R_0402_1005Metric
R18: 13.7k; R_0402_1005Metric
R19: 249k; R_0402_1005Metric; not fitted
TP1, TP2, TP3: TestPoint; TestPoint_Pad_D0.8mm
U2: ISL854102FRZ-T; DFN-12-1EP_3x4mm_P0.5mm_EP1.7x3.3mm

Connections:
+5V: D3.1 (K), R11.2, TP1.1; also elsewhere on the board
GND: C15.2, C16.2, C17.2, C18.2, C19.2, C20.2, C22.2, C23.2, J4.2, J4.3, R18.2, R21.2, R22.2, U2.6 (PGND), U2.13 (GNDPAD); also elsewhere on the board
unnamed: C13.1, C19.1
unnamed: C14.1, C15.1, C16.1, C17.1, C18.1, L3.2, R11.1, R13.1
unnamed: C22.1, R19.2
unnamed: C13.2, D2.1 (K), TP2.1, U2.4 (VIN), U2.7 (EN)
unnamed: C12.1, U2.3 (BOOT)
unnamed: C23.1, R19.1, R20.1, U2.11 (COMP)
unnamed: C14.2, R13.2, R18.1, U2.10 (FB)
unnamed: R21.1, R22.1, U2.12 (FS)
unnamed: C12.2, L3.1, U2.5 (PHASE)
unnamed: C20.1, R12.1, R20.2, U2.1 (SS), U2.9 (VCC)
unnamed: R12.2, U2.2 (SYNC)
VBUS: D3.2 (A); also elsewhere on the board
VCC: D2.2 (A), J4.1, TP3.1; also elsewhere on the board

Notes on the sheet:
SCHOTTKY FOR REVERSE POLARITY PROTECTION
BUCK CONVERTER
DC JACK
SCHOTTKY FOR USB OVERVOLTAGE PROTECTION
